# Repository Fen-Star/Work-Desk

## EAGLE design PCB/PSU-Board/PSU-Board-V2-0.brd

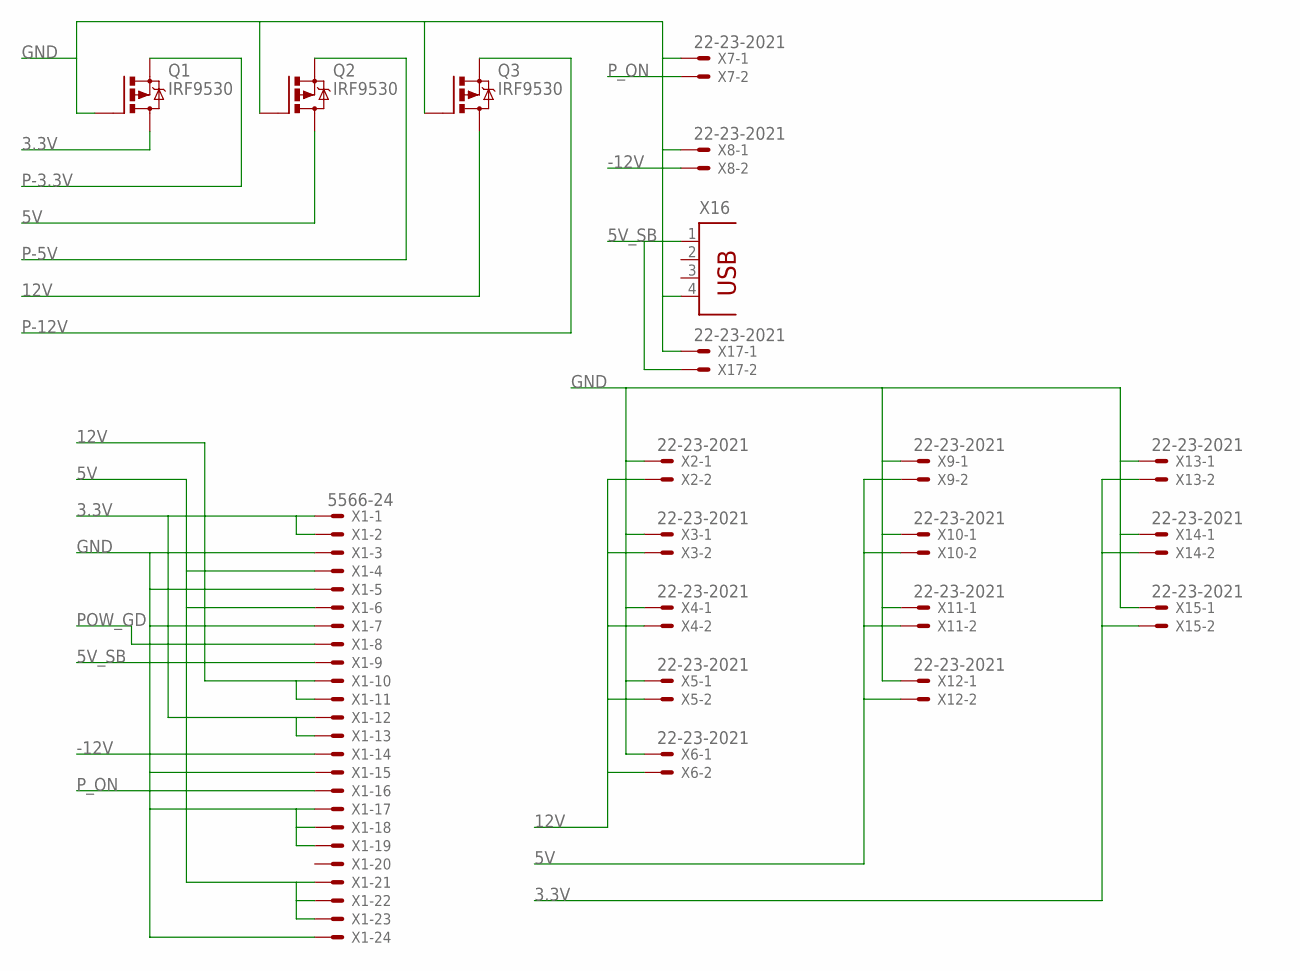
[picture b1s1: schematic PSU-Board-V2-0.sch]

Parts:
Q1, Q2, Q3: IRF9530; TO220BV
X1: 5566-24
X2, X3, X4, X5, X6, X7, X8, X9, X10, X11, X12, X13, X14, X15, X17: 22-23-2021
X16: PN87520

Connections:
3.3V: Q1.D, X1.1, X1.2, X1.12, X1.13, X13.2, X14.2, X15.2
5V: Q2.D, X1.4, X1.6, X1.21, X1.22, X1.23, X9.2, X10.2, X11.2, X12.2
5V_SB: X1.9, X16.1, X17.2
12V: Q3.D, X1.10, X1.11, X2.2, X3.2, X4.2, X5.2, X6.2
-12V: X1.14, X8.2
GND: Q1.G, Q2.G, Q3.G, X1.3, X1.5, X1.7, X1.15, X1.17, X1.18, X1.19, X1.24, X2.1, X3.1, X4.1, X5.1, X6.1, X7.1, X8.1, X9.1, X10.1, X11.1, X12.1, X13.1, X14.1, X15.1, X16.4, X17.1
P-3.3V: Q1.S
P-5V: Q2.S
P-12V: Q3.S
POW_GD: X1.8
P_ON: X1.16, X7.2

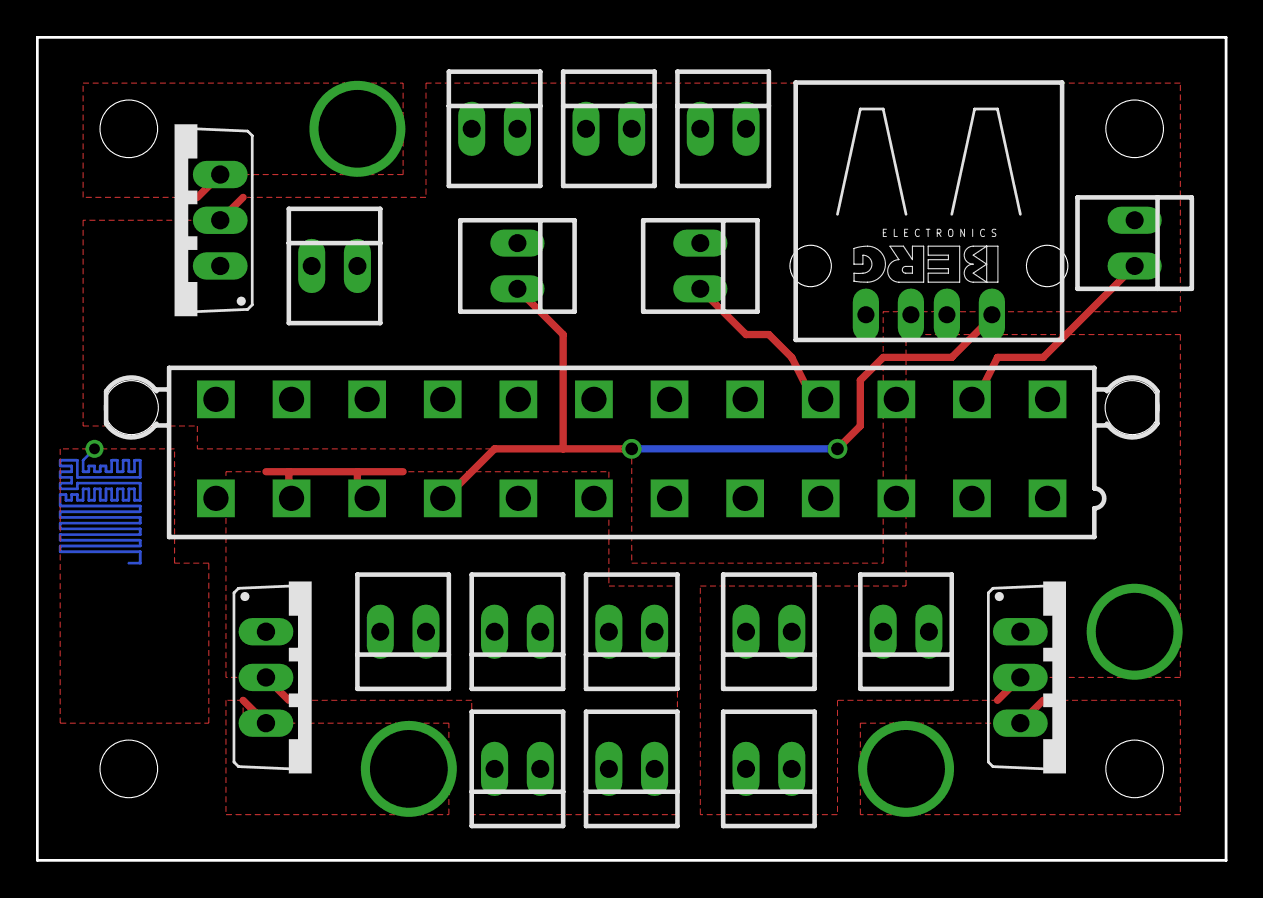
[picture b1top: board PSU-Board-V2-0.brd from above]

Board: 2 copper layers, 66.0 x 45.7 mm, 20 parts (0 on the bottom side), 7 nets.

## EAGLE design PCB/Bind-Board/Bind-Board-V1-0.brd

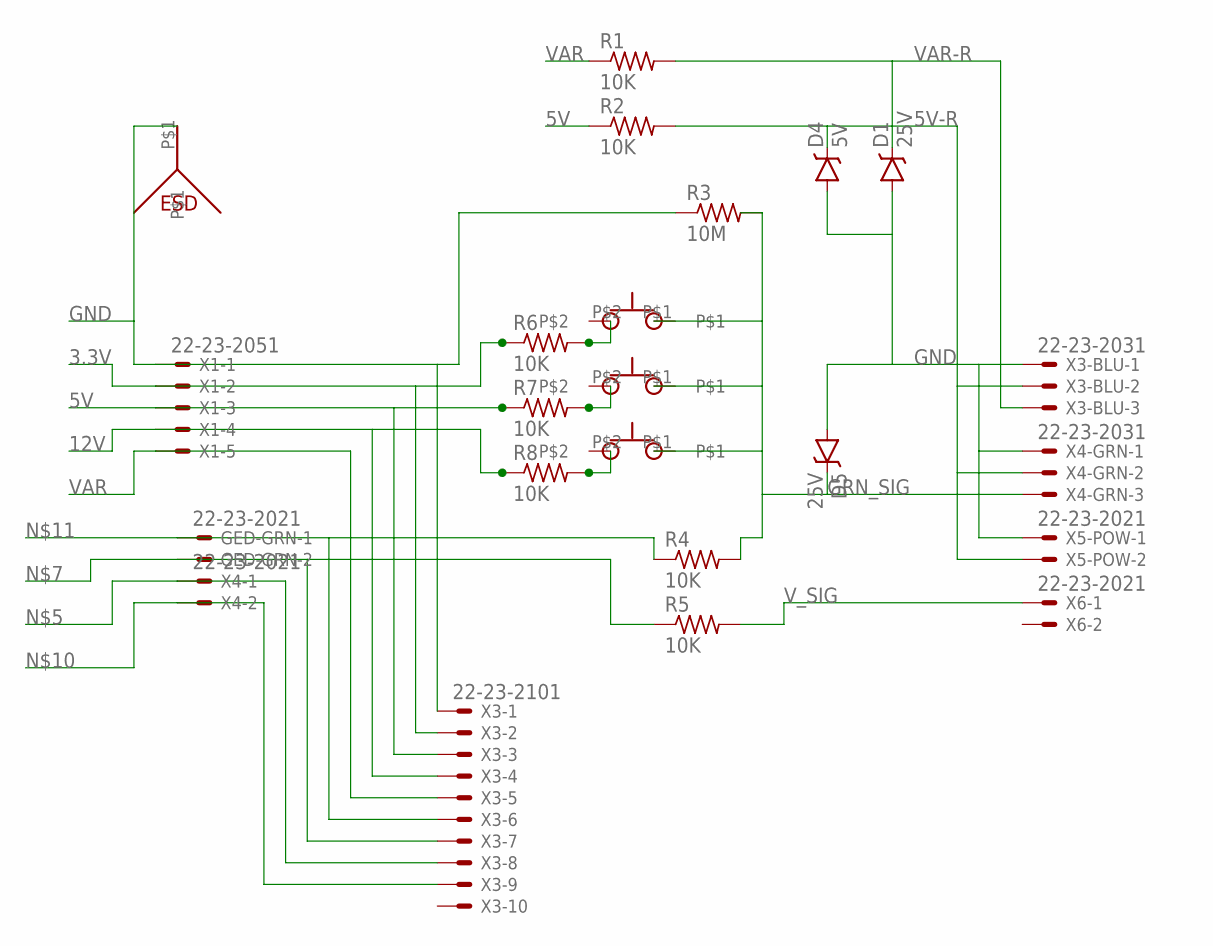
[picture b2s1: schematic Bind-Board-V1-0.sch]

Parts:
D1, D5: 25V; SOT23-3
D4: 5V; SOT23-3
GED-GRN: 22-23-2021
R1, R2, R4, R5, R6, R7, R8: 10K; M2012
R3: 10M; M2012
U$1, U$2, U$3: PUSH-BUTTON-SWITCH
U$4: ESD-STAR
X1: 22-23-2051
X3: 22-23-2101
X3-BLU, X4-GRN: 22-23-2031
X4, X5-POW, X6: 22-23-2021

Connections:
3.3V: R6.1, X1.2, X3.2
5V: R2.1, R7.1, X1.3, X3.3
5V-R: D4.3 (C), R2.2, X3-BLU.2, X4-GRN.2, X5-POW.2
12V: R8.1, X1.4, X3.4
GND: D1.1 (A), D4.1 (A), D5.1 (A), R3.1, U$4.P$1, X1.1, X3.1, X3-BLU.1, X4-GRN.1, X5-POW.1
GRN_SIG: D5.3 (C), R3.2, R4.2, U$1.P$1, U$2.P$1, U$3.P$1, X4-GRN.3
unnamed: R7.2, U$2.P$2
unnamed: R6.2, U$1.P$2
unnamed: R8.2, U$3.P$2
unnamed: X3.8, X4.1
unnamed: GED-GRN.2, R5.1, X3.7
unnamed: X3.9, X4.2
unnamed: GED-GRN.1, R4.1, X3.6
VAR: R1.1, X1.5, X3.5
VAR-R: D1.3 (C), R1.2, X3-BLU.3
V_SIG: R5.2, X6.1

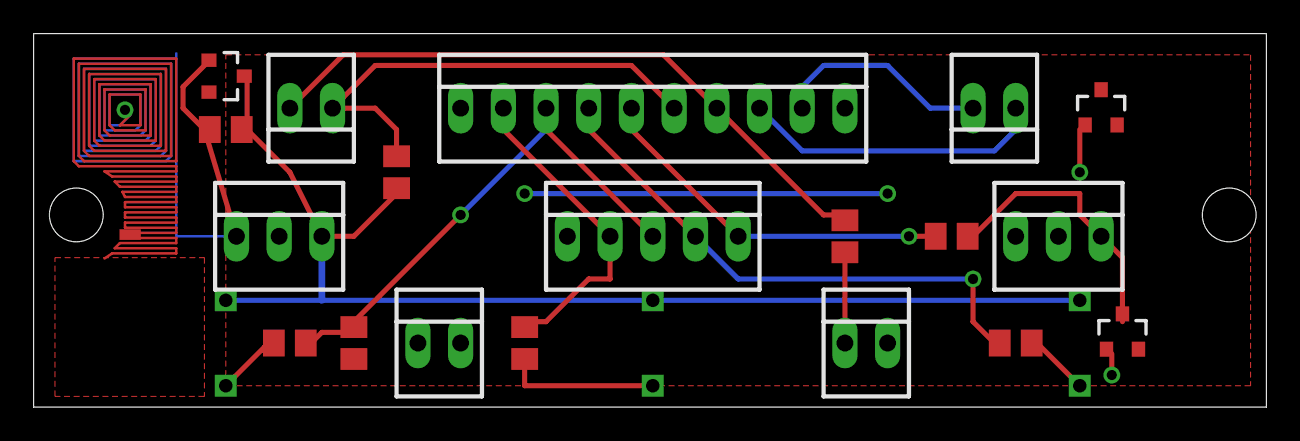
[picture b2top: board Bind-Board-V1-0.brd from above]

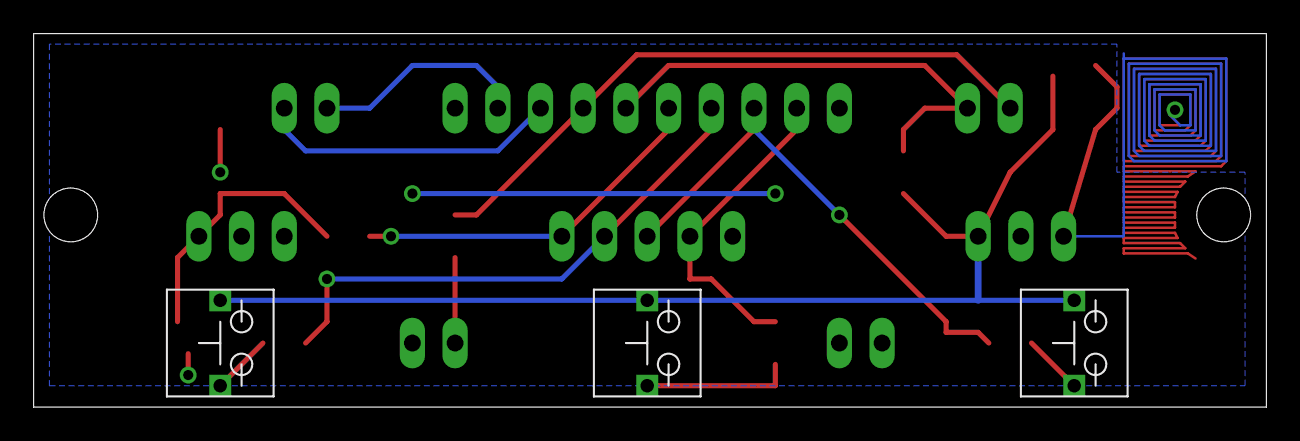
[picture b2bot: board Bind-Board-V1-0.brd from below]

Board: 2 copper layers, 73.3 x 22.2 mm, 23 parts (3 on the bottom side), 16 nets.

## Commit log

2015-09-12 :tada: Added .gitattributes & .gitignore files
2015-09-12 Abort, retry, fail
2015-09-12 Add readme, remove extra bind post
2015-09-12 Added PCB files

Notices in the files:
PCB/Bind-Board/Bind-Board-V1-0.brd:
© 2015
PCB/PSU-Board/PSU-Board-V2-0.brd:
© Wesley Rogers 2015 ATX power breakout board REV 2.0
parts and their libraries:
SparkFun-DiscreteSemi: Licensing: Creative Commons ShareAlike 4.0 International - https://creativecommons.org/licenses/by-sa/4.0
